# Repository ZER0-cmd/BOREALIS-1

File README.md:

%20(2).png)
# Från klassrummen till rymden, en röd tråd från nyfikenhet till framtidens ingenjörer!
BOREALIS är ett projekt för högstadieelever som syftar till att introducera unga till teknik och rymdforskning genom praktiska, rymdnära experiment anpassade till deras kunskapsnivå. Genom att designa och bygga små experiment som skickas upp med stratosfäriska ballonger får eleverna uppleva ett verkligt rymdprojekt, vilket ger dem en första inblick i rymdteknik och ingenjörskonst. Projektet är utformat för att passa den grundläggande förståelse för naturvetenskap som elever på högstadiet har, och fungerar som en inspirerande introduktion till STEM-ämnen och framtida rymdrelaterade projekt.

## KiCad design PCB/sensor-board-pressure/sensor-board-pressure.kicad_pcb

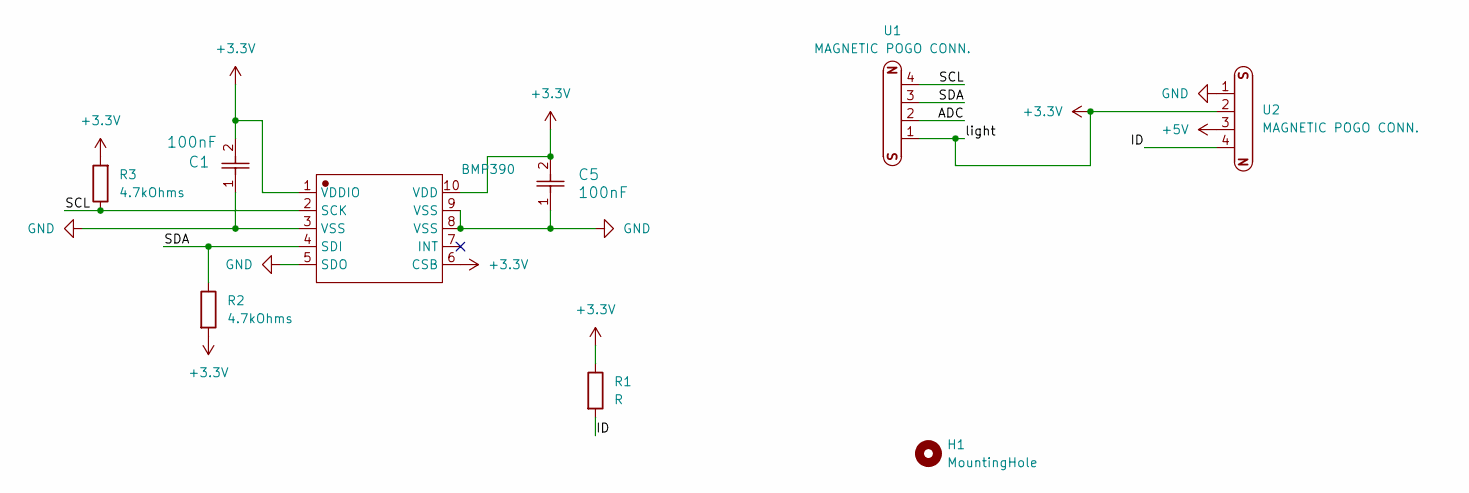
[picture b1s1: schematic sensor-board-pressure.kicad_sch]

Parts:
BMP390: BMP388
C1, C5: 100nF; C_0805_2012Metric
H1: MountingHole; MountingHole_2.7mm_M2.5_Pad
R1: R; R_0805_2012Metric
R2, R3: 4.7kOhms; R_0805_2012Metric
U1, U2: MAGNETIC POGO CONN.

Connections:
+3.3V: BMP390.1 (VDDIO), BMP390.6 (CSB), BMP390.10 (VDD), C1.2, C5.2, R1.1, R2.2, R3.2, U1.1, U2.2
+5V: U2.3
/ADC: U1.2
/ID: R1.2, U2.4
/SCL: BMP390.2 (SCK), R3.1, U1.4
/SDA: BMP390.4 (SDI), R2.1, U1.3
GND: BMP390.3 (VSS), BMP390.5 (SDO), BMP390.8 (VSS), BMP390.9 (VSS), C1.1, C5.1, U2.1

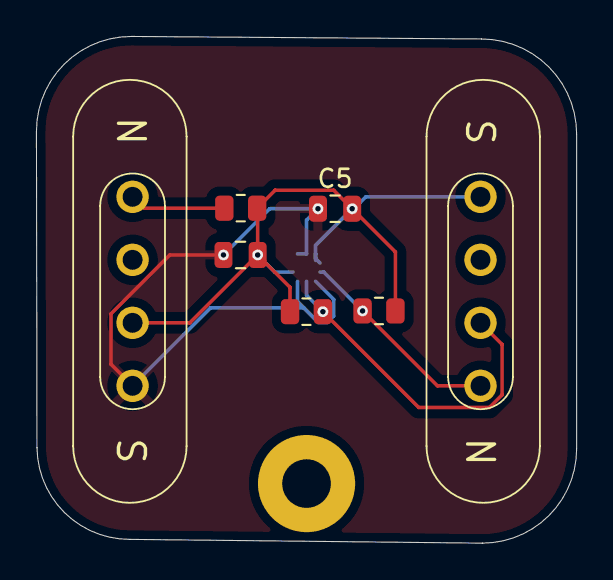
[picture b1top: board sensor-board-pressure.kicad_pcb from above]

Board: 2 copper layers, 30.0 x 28.1 mm, 9 parts (1 on the bottom side), 5 nets.

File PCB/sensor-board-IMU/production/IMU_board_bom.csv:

Designator,Footprint,Quantity,Value,LCSC Part #
"C1, C5",0805,2,0.1uF,
C2,0805,1,10nF,
MPU6500,mpu6500,1,~,
R1,0805,1,R,
"R2, R3",0805,2,4.7k,
"U1, U2",MAGNETIC POGO CONN.,2,MAGNETIC POGO CONN.,

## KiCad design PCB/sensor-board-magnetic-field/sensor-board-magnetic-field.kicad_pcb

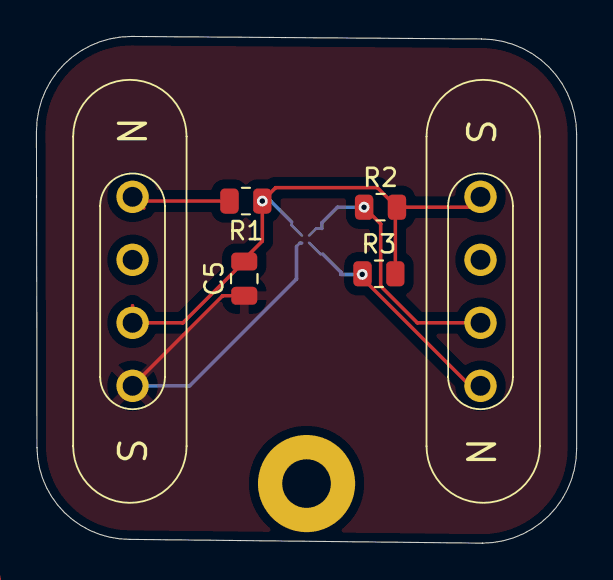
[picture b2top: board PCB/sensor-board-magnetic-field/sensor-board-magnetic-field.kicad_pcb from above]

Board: 2 copper layers, 30.0 x 28.1 mm, 8 parts (1 on the bottom side), 5 nets.

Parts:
C5: 2.2uf; C_0805_2012Metric
H1: MountingHole; MountingHole_2.7mm_M2.5_Pad
MMC5603NJ1: XDCR_MMC5603NJ
R1: R; R_0805_2012Metric
R2, R3: 2.7k; R_0805_2012Metric
U1, U2: MAGNETIC POGO CONN.

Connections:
+3.3V: C5.2, MMC5603NJ1.B1 (VDD), R1.1, R2.2, R3.2, U1.1, U2.2
/ID: R1.2, U2.4
/SCL: MMC5603NJ1.A2 (SCL), R3.1, U1.4
/SDA: MMC5603NJ1.B2 (SDA), R2.1, U1.3
GND: C5.1, MMC5603NJ1.A1 (VSA), U2.1

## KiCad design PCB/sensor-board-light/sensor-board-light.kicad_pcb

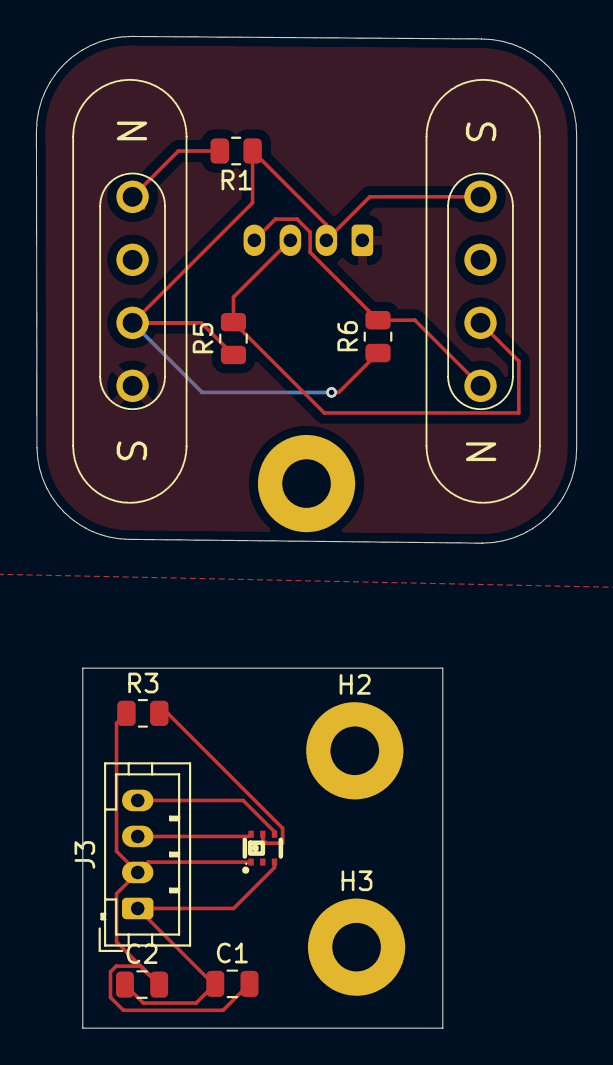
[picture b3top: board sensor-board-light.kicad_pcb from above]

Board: 2 copper layers, 30.0 x 55.1 mm, 14 parts (1 on the bottom side), 9 nets.

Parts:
C1: 0.1uF; C_0805_2012Metric
C2: 4.7uF; C_0805_2012Metric
H1, H2, H3: MountingHole; MountingHole_2.7mm_M2.5_Pad
J1, J3: Conn_01x04_Pin; JST_PH_B4B-PH-K_1x04_P2.00mm_Vertical
LTR-390UV-01: SENSOR-SMD_LTR-390UV-01
R1: R; R_0805_2012Metric
R3, R5, R6: 10k; R_0805_2012Metric
U1, U2: MAGNETIC POGO CONN.

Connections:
+3.3V: J1.2, R1.1, R5.1, R6.1, U1.1, U2.2
/3.3v: C1.2, C2.2, J3.2, LTR-390UV-01.1 (VDD), R3.1
/ID: R1.2, U2.4
/SCL: J1.4, R6.2, U1.4
/SCL1: J3.4, LTR-390UV-01.4 (SCL)
/SDA: J1.3, R5.2, U1.3
/SDA1: J3.3, LTR-390UV-01.6 (SDA)
GND: C1.1, C2.1, J1.1, J3.1, LTR-390UV-01.3 (GND), U2.1
unnamed: LTR-390UV-01.5 (INT), R3.2

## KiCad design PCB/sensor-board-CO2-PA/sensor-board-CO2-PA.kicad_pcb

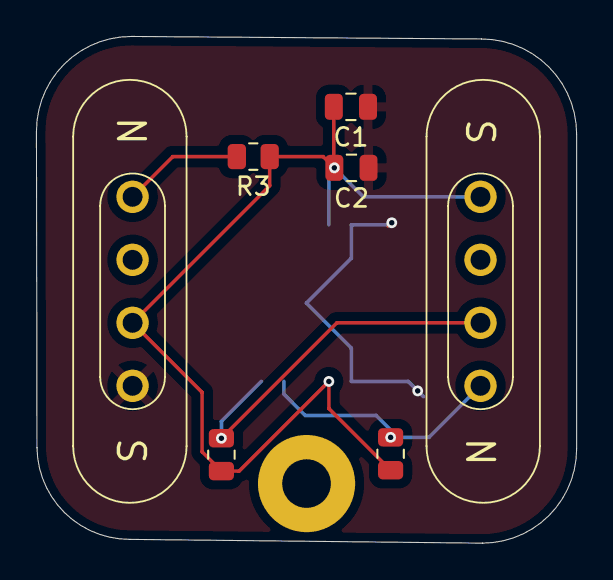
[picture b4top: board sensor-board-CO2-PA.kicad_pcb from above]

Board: 2 copper layers, 30.0 x 28.2 mm, 9 parts (1 on the bottom side), 5 nets.

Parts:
C1: 10microf; C_0805_2012Metric
C2: 0.1uf; C_0805_2012Metric
H1: MountingHole; MountingHole_2.7mm_M2.5_Pad
R1: 10K; R_0805_2012Metric
R2: 10k; R_0805_2012Metric
R3: R; R_0805_2012Metric
U1, U2: MAGNETIC POGO CONN.
U1#2: SCD40-D-R2; SCD40 footprint

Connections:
+3.3V: C1.2, C2.2, R1.1, R2.1, R3.1, U1.1, U1#2.7 (VDD), U1#2.19 (VDDH), U2.2
/ID: R3.2, U2.4
/SCL: R2.2, U1.4, U1#2.9 (SCL)
/SDA: R1.2, U1.3, U1#2.10 (SDA)
GND: C1.1, C2.1, U1#2.6 (GND), U1#2.20 (GND), U1#2.21 (GND), U2.1

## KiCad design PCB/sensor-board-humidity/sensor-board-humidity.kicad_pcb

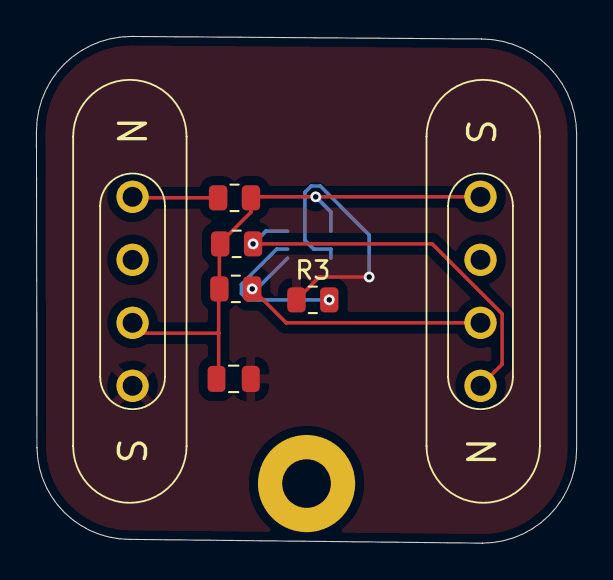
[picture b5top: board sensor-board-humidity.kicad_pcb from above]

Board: 2 copper layers, 30.0 x 28.1 mm, 9 parts (1 on the bottom side), 6 nets.

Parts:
C5: 100nf; C_0805_2012Metric
H1: MountingHole; MountingHole_2.7mm_M2.5_Pad
R1: R; R_0805_2012Metric
R3, R4, R5: 10k; R_0805_2012Metric
SHT31: sht31-footprint
U1, U2: MAGNETIC POGO CONN.

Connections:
+3.3V: C5.1, R1.1, R4.1, R5.2, SHT31.5 (VDD), U1.1, U2.2
/ID: R1.2, U2.4
/SCL: R4.2, SHT31.4 (SCL), U1.4
/SDA: R5.1, SHT31.1 (SDA), U1.3
GND: C5.2, R3.1, SHT31.7 (R), SHT31.8 (VSS), SHT31.9 (EP), U2.1
unnamed: R3.2, SHT31.2 (ADDR)

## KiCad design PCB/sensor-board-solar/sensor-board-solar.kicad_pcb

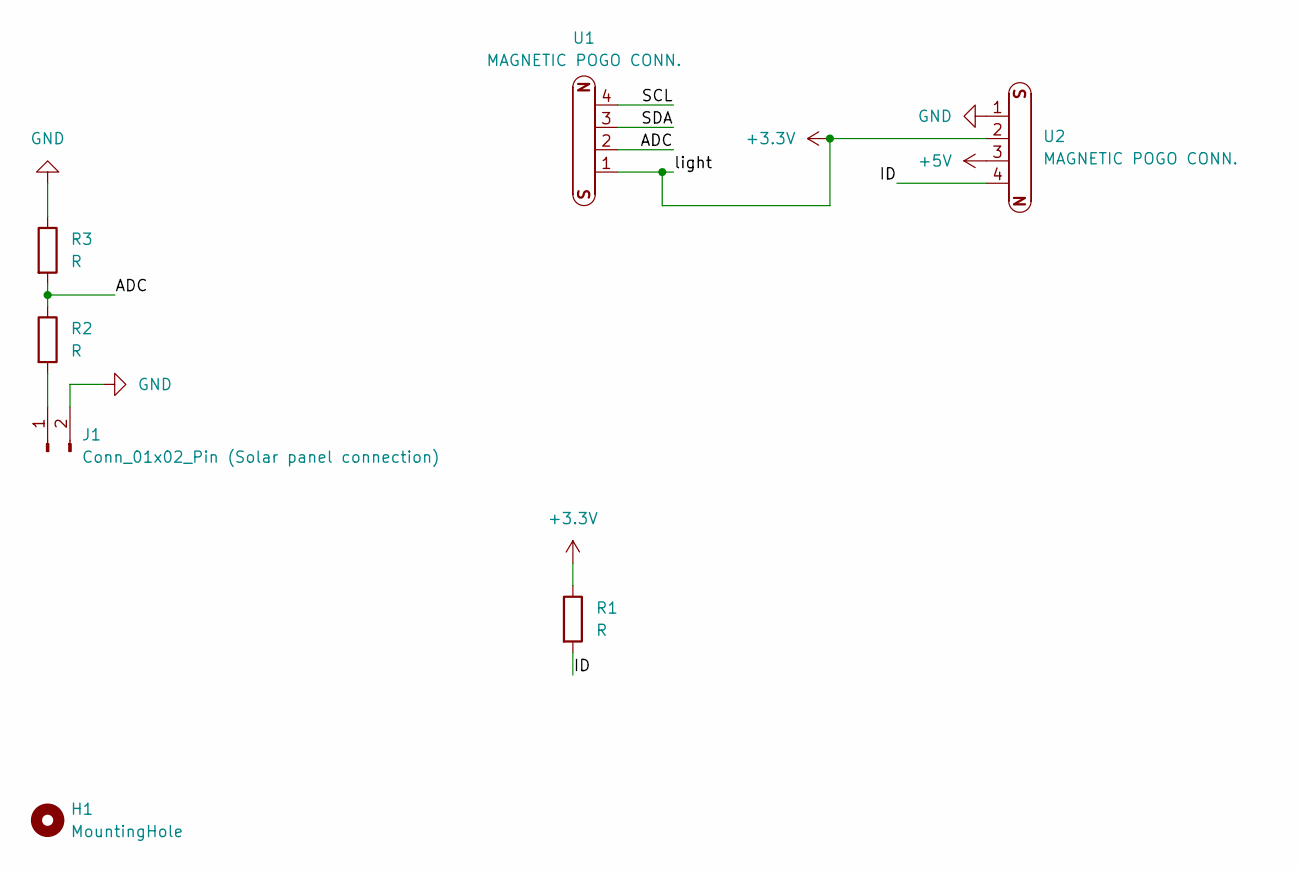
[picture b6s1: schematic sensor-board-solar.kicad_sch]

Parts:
H1: MountingHole; MountingHole_2.7mm_M2.5_Pad
J1: Conn_01x02_Pin (Solar panel connection); JST_PH_B2B-PH-K_1x02_P2.00mm_Vertical
R1, R2, R3: R; R_0805_2012Metric
U1, U2: MAGNETIC POGO CONN.

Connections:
+3.3V: R1.1, U1.1, U2.2
+5V: U2.3
/ADC: R2.1, R3.2, U1.2
/ID: R1.2, U2.4
/SCL: U1.4
/SDA: U1.3
GND: J1.2, R3.1, U2.1
unnamed: J1.1, R2.2

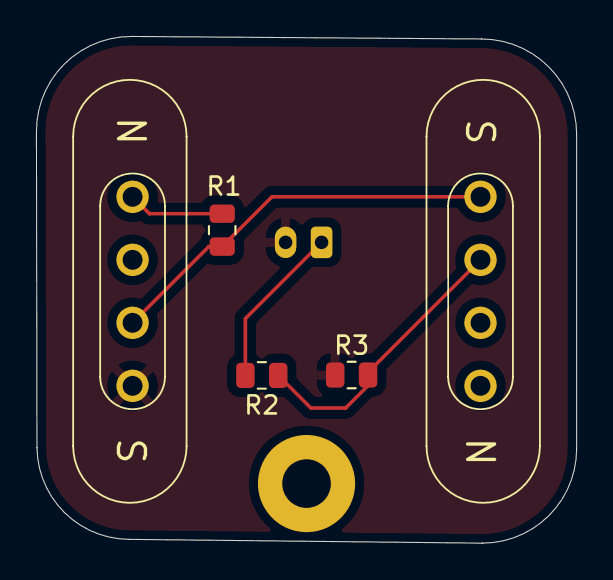
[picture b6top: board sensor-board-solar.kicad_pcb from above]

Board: 2 copper layers, 30.0 x 28.1 mm, 7 parts (1 on the bottom side), 5 nets.

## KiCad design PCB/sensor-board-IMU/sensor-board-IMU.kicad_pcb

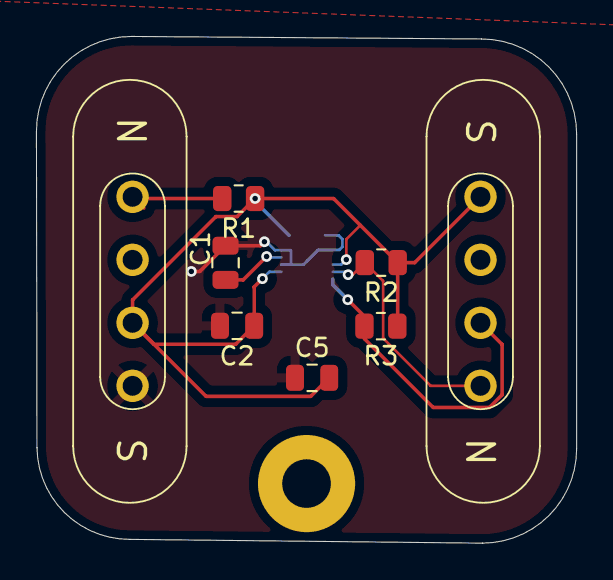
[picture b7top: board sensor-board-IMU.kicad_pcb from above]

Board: 2 copper layers, 30.0 x 28.1 mm, 10 parts (1 on the bottom side), 6 nets.

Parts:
C1: 0.1uF; C_0805_2012Metric
C2: 10nF; C_0805_2012Metric
C5: 0.1uf; C_0805_2012Metric
H1: MountingHole; MountingHole_2.7mm_M2.5_Pad
MPU6500: mpu6500
R1: R; R_0805_2012Metric
R2, R3: 4.7k; R_0805_2012Metric
U1, U2: MAGNETIC POGO CONN.

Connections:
+3.3V: C2.1, C5.2, MPU6500.8 (VDDIO), MPU6500.13 (VDD), MPU6500.22 (nCS), R1.1, R2.1, R3.1, U1.1, U2.2
/ID: R1.2, U2.4
/SCL: MPU6500.23 (SCL/SCLK), R2.2, U1.4
/SDA: MPU6500.24 (SDA/SDI), R3.2, U1.3
GND: C1.2, C2.2, C5.1, MPU6500.9 (SDO/AD0), MPU6500.11 (FSYNC), MPU6500.18 (GND), MPU6500.20 (RESV), MPU6500.25 (EP), U2.1
unnamed: C1.1, MPU6500.10 (REGOUT)

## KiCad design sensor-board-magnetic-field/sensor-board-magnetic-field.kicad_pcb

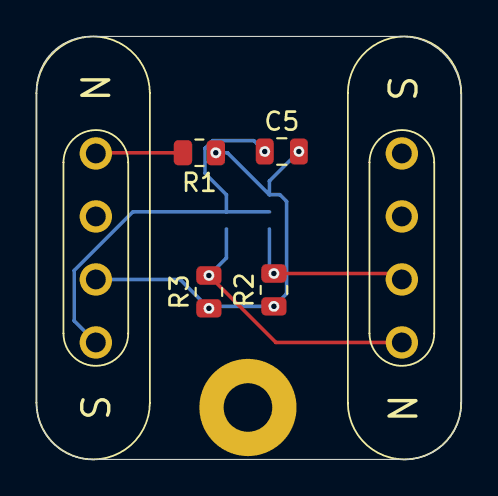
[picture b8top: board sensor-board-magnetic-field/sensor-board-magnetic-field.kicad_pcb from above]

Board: 2 copper layers, 23.6 x 23.5 mm, 8 parts (1 on the bottom side), 5 nets.

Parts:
C5: 100nF; C_0805_2012Metric
H1: MountingHole; MountingHole_2.7mm_M2.5_Pad
R1: R; R_0805_2012Metric
R2, R3: 10K; R_0805_2012Metric
TLV493D1: TLV493D
U1, U2: MAGNETIC POGO CONN.

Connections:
+3.3V: C5.2, R1.1, R2.1, R3.1, TLV493D1.4 (VDD), U2.2
/ID: R1.2, U2.4
/SCL: R3.2, TLV493D1.1 (SCL/INT), U1.4
/SDA: R2.2, TLV493D1.6 (SDA/ADDR), U1.3
GND: C5.1, TLV493D1.2 (GND), TLV493D1.3 (GND), TLV493D1.5 (GND), U2.1

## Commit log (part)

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2026-02-09 Update LICENSE
2026-02-15 Update PCB files (pressure + solar)#
2026-02-16 made some changes
2026-02-17 Add image to README for visual enhancement
    Added an image to enhance the README content.
2026-02-17 Made some final checks and changes
2026-02-22 Add files via upload
    Added sample data
2026-02-22 bug fix
2026-02-22 bug fix
    fixed crash when multiple plotters
    general optimization
2026-02-22 Added datapoint markers
    More optimization.
    Added modes for scatter, plot and both.
    Small tweaks in functionality
2026-02-22 Update module_eng.py
    Added functionality to change labels
2026-02-22 Update module_eng.py
    Added typevalue support
2026-02-22 Update module_eng.py
    fixed errors
2026-02-22 Update module_eng.py
    added redundancy
2026-02-23 Update module_swe.py
    New version based on the english one
2026-03-07 Test
2026-03-07 Update module_eng.py
    Added support for inverted y and x axis
2026-03-07 Update module_eng.py
    Redundancy
2026-03-09 New documentation
2026-03-09 More documentation
2026-03-10 Sourced new sensor libraries
2026-03-11 Updated files: Note not done
2026-03-11 Documetnation
2026-03-11 Fixed issue with documentation
2026-03-20 Cleanup
2026-03-20 blah blah blah
2026-03-20 blah blah blah added some stuff
2026-03-20 generalized data writing
2026-03-20 Impoved understandbility of the code
2026-03-20 UI picture support
2026-03-21 making some changes
2026-03-21 fixed picture
2026-03-21 Actually fixed picture
2026-03-21 added sd detect functionality
2026-03-21 LED works now!
2026-03-21 added some sensor stuff
2026-03-21 made some sensor changes
2026-03-22 made soem changes
2026-03-22 blah
2026-03-22 awesrtrdhytj
2026-03-22 formating fix
2026-03-22 pictues!
2026-03-22 things
2026-03-22 fixed blinking
2026-03-22 hugyioji
2026-03-22 adojif
2026-03-22 akdhifjo
2026-03-22 more pictures!
2026-03-22 asldfj
2026-04-04 fixed ui sensor init issue
2026-04-05 sodhfuo9aipefjo0qew9uprhf+u9¨qea
2026-04-13 stuff
2026-04-13 flipped OLED. Improved SD logging protocol
2026-04-21 Fixed interface
2026-04-21 fixed reset
2026-04-27 Streamlined sensor idntification + added identification of more sensors
2026-04-30 Solar sensor test1
2026-04-30 Cahnged to ain2
2026-05-01 Sensors!!!! (good enough)
2026-05-03 Here you go Hasan
2026-05-06 trust
2026-05-08 waserdtfy
2026-05-10 Pls work
2026-05-10 Pls work x1000
2026-05-13 agffhjh
2026-05-15 caalibration
2026-05-15 fixes?
2026-05-16 more fix
2026-05-17 asadfa
2026-05-17 direct firmaware incorporation + developer methods + small bug fix
2026-05-24 proto
2026-05-24 listfile
2026-05-24 fixed typo ish
2026-05-31 logo fix
2026-05-31 sdada
2026-06-01 Create data.csv
    fil till berzan
2026-06-01 copilot is thinking # bro is the tinker
2026-06-01 del sys32
2026-06-01 Rename column 'Höjd_m' to 'Alt_m' in CSV file
2026-06-01 data
2026-06-10 set time script
2026-06-10 ahhh
